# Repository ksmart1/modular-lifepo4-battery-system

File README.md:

# modular-lifepo4-battery-system
A modular LiFePO₄ battery platform with integrated monitoring, protection, and expansion.
 
# Overview

This repository documents the design and implementation of a modular LiFePO₄ battery system intended for portable power, backup energy storage, and future expansion.

The project spans power electronics, PCB design, battery management, manufacturing constraints, and mechanical considerations, and was developed iteratively with a strong emphasis on safety, serviceability, and real-world manufacturability.

## The system is composed of:

  - A battery pack PCB (2-layer and 4-layer variants)

  - A “Brain Board” responsible for regulation, monitoring, and control

  - Optional expansion / I/O boards to support charging and load sharing

  - Future 3D-printed mechanical enclosures

### Key Features

  - LiFePO₄ chemistry for improved safety and cycle life

  - Modular architecture (scalable from 4S to 8S and beyond)

  - Common-port BMS compatibility

  - High-current copper pours and busbar-style routing

  - Sense resistor–based current measurement

  - TVS, fusing, and transient protection

  - Designed for both hand assembly and low-volume fabrication

### System Architecture
  - Battery Pack PCB

  - Supports prismatic LiFePO₄ cells

  - Series connections implemented using large copper pours

  - Balance taps routed cleanly using net ties to avoid schematic ambiguity

  - Sense resistor footprint sized for tens of amps

  - Test points included for validation and debugging

### Designed in both:

  - 2-layer (cost-optimized)

  - 4-layer (improved current return and EMI behavior)

### Protection & Power Path

  - Polyfuse (40A) for fault protection

  - TVS diodes (58V) placed at charge and input connectors

  - Local ceramic decoupling at every high-current connector

### Clear separation between:

  - Battery input

  - Charger input

  - Load output

  - Brain Board

  - Buck regulation for system rails

  - MCU-based control and monitoring

  - Fuel gauge integration (BQ34Z100 family)

  - LED state-of-charge indicators

  - Designed to mate cleanly with multiple battery variants

## Design Considerations

### Manufacturing constraints were a first-class concern:

  - OSH Park vs JLCPCB tradeoffs

  - ENIG vs HASL finish

  - Stencil ordering and hand-assembly feasibility

### Hand soldering viability:

  - Component choices intentionally avoided unnecessary fine-pitch parts

  - Sense resistor installation planned explicitly for hand soldering

### Safety over aesthetics:

  - Wide copper, conservative spacing, robust grounding

### Debuggability:

  - Generous test points

  - Logical net naming

  - Clear silkscreen labeling

  - Mechanical Integration

  - PCB dimensions intentionally oversized relative to cell geometry

  - Designed to bolt into a 3D-printed, topless battery casement

### Enclosure design considers:

  - Foam isolation between cells

  - Modular splitting for printer size limitations

  - Future dovetail or fastener-based joining

### Tools & Technologies

  - KiCad (schematic + PCB layout)

  - OSH Park / JLCPCB (fabrication)

  - Inkscape (labeling / graphics)

  - 3D printing (mechanical planning)

  - Hand SMT soldering (assembly)

## Why This Project Matters

### This project demonstrates:

  - Practical power electronics design

  - Battery system safety awareness

  - PCB layout for high-current applications

  - Iterative engineering problem-solving

  - Comfort across hardware, software-adjacent design, and manufacturing

  - It reflects the type of work required in embedded systems, hardware engineering, robotics, energy systems, and applied cybersecurity/assurance roles where understanding      the entire system matters.

### Status

  - Battery PCB (4S and 8S variants): Complete

  - Expansion / I/O board: Complete

  - Assembly and validation: In progress

  - Enclosure design: Complete

  - Future revisions: Expected

Disclaimer

This project is for educational and experimental purposes.
Working with high-current lithium batteries carries inherent risk.
Use appropriate safety precautions and do not deploy designs without proper validation.

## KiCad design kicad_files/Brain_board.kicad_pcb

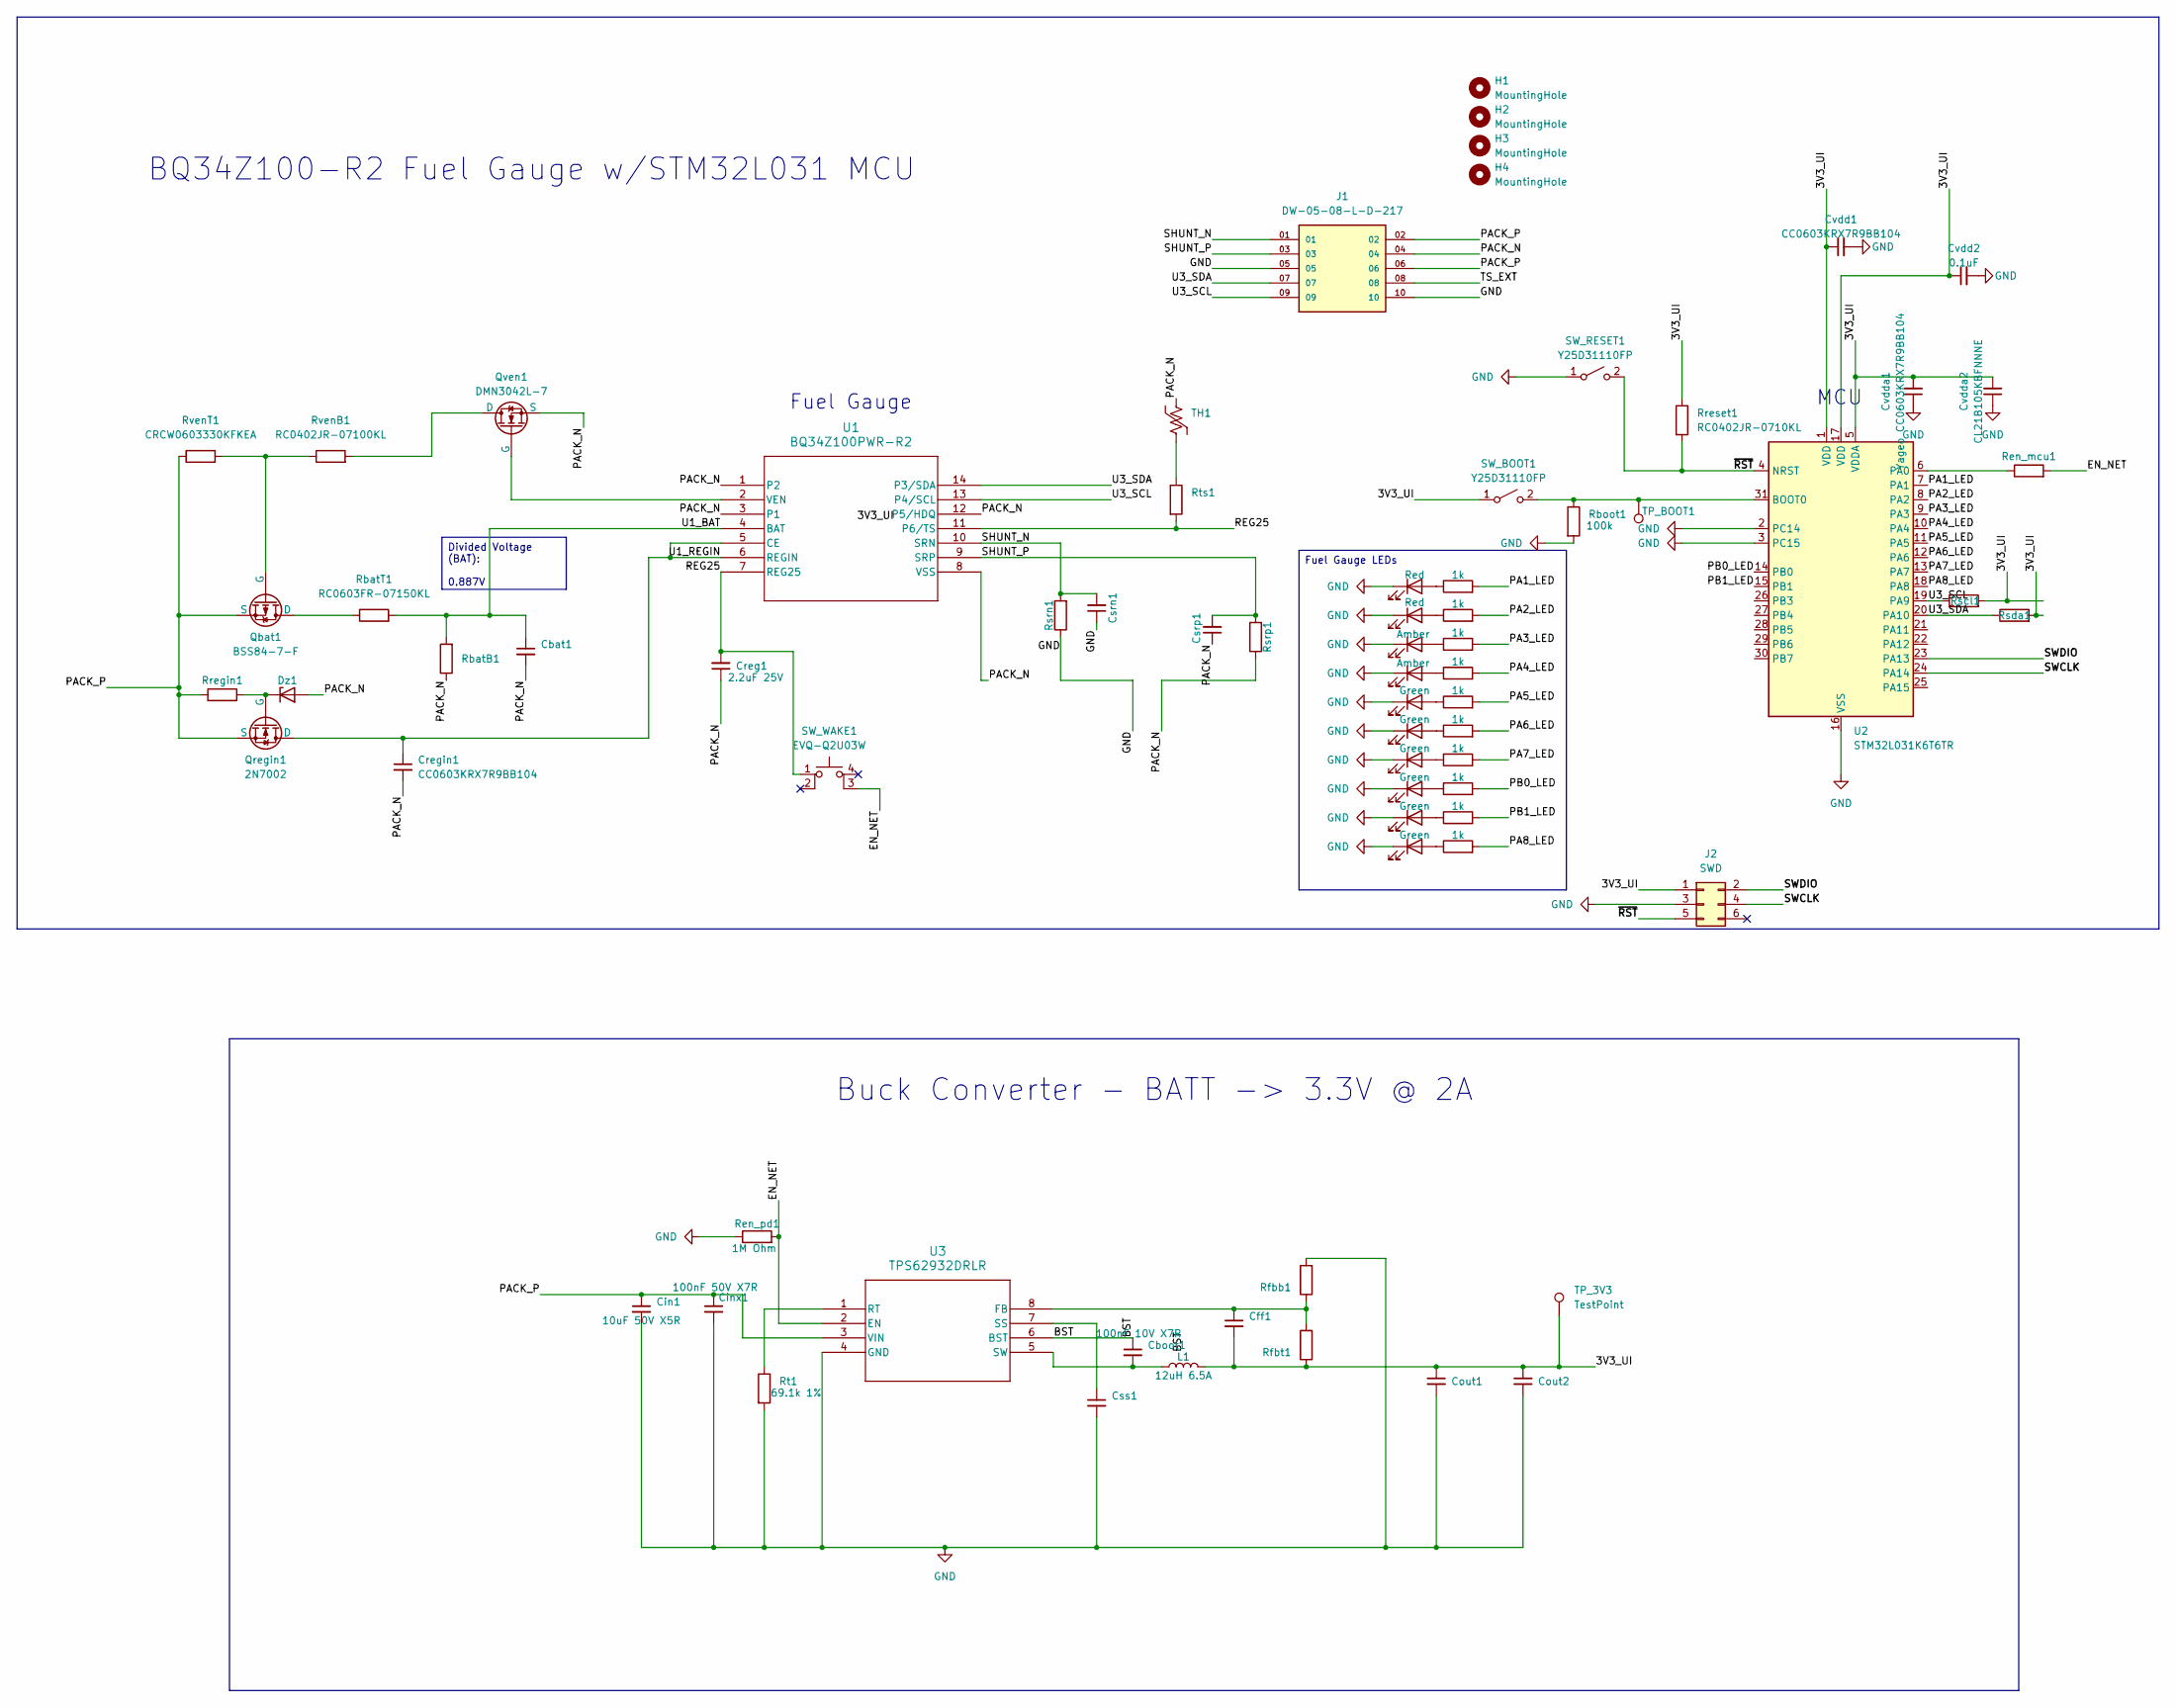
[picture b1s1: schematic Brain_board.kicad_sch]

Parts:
Cbat1: GRM1885C1H332JA01D; C_0603_1608Metric
Cboot1: CC0603KRX7R9BB104; C_0603_1608Metric
Cff1: C0603C560J5GACTU; C_0603_1608Metric
Cin1: CL31A106KBHNNNE; C_1206_3216Metric
Cinx1: CC0603KRX7R9BB104; C_0603_1608Metric
Cout1: GRM31CR61A476ME15L; C_1210_3225Metric
Cout2: GRM32ER61C476KE15L; C_1210_3225Metric
Creg1: GMC10X7R225K25NT; C_0603_1608Metric
Cregin1: CC0603KRX7R9BB104; C_0603_1608Metric
Csrn1: CC0603KRX7R9BB104; C_0603_1608Metric
Csrp1: CC0603KRX7R9BB104; C_0603_1608Metric
Css1: GRM155R71A333KA01D; C_0402_1005Metric
Cvdd1: CC0603KRX7R9BB104; C_0603_1608Metric
Cvdd2: 0.1uF; C_0603_1608Metric
Cvdda1: Yageo CC0603KRX7R9BB104; C_0603_1608Metric
Cvdda2: CL21B105KBFNNNE; C_0805_2012Metric
D1, D2, D3, D4, D5, D6: 5988170107F; LED_0805_2012Metric_Pad1.15x1.40mm_HandSolder
D7, D8: B1701UY--20D000214U1930; LED_0805_2012Metric_Pad1.15x1.40mm_HandSolder
D9, D10: B1701URO-20D000114U1930; LED_0805_2012Metric_Pad1.15x1.40mm_HandSolder
Dz1: BZT52C5V6T-7; D_SOD-523
H1, H2, H3, H4: MountingHole; MountingHole_3.2mm_M3
J1: DW-05-08-L-D-217; SAMTEC_DW-05-X-X-D-X; PARTREV 01-06-94
J2: SWD; CON6_2X3_DU_FTSH_SAI
L1: SRR1208-120ML; L_Bourns_SRR1208_12.7x12.7mm
Qbat1: BSS84-7-F; SOT-23-3
Qregin1: 2N7002; SOT-23-3
Qven1: DMN3042L-7; SOT-23-3
RbatB1: RC0603FR-074K7L; R_0603_1608Metric
RbatT1: RC0603FR-07150KL; R_0603_1608Metric
Rboot1: RC0402JR-07100KL; R_0402_1005Metric
Ren_mcu1: RC0402JR-0710KL; R_0402_1005Metric
Ren_pd1: CRCW06031M00FKEA; R_0603_1608Metric
Rfbb1: RC0402JR-0710KL; R_0402_1005Metric
Rfbt1: CRCW040230K9FKED; R_0402_1005Metric
Rled1, Rled2, Rled3, Rled4, Rled5, Rled6, Rled7, Rled8, Rled9, Rled10: RMCF0603FT1K00; R_0603_1608Metric_Pad0.98x0.95mm_HandSolder
Rregin1: RC0402JR-0710KL; R_0402_1005Metric
Rreset1: RC0402JR-0710KL; R_0402_1005Metric
Rscl1: RC0603FR-074K7L; R_0402_1005Metric
Rsda1: RC0603FR-074K7L; R_0402_1005Metric
Rsrn1: CRCW0603100RFKEA; R_0603_1608Metric
Rsrp1: CRCW0603100RFKEA; R_0603_1608Metric
Rt1: CRCW060361K9FKEA; R_0603_1608Metric
Rts1: RC0402JR-0710KL; R_0402_1005Metric
RvenB1: RC0402JR-07100KL; R_0402_1005Metric
RvenT1: CRCW0603330KFKEA; R_0603_1608Metric
SW_BOOT1: Y25D31110FP; KXT 311 LHS_CNK
SW_RESET1: Y25D31110FP; KXT 311 LHS_CNK
SW_WAKE1: EVQ-Q2U03W; EVQQ2_3_PAN
TH1: 103KT1608T-1P; R_0603_1608Metric
TP_3V3: TestPoint; TestPoint_Pad_D1.5mm
TP_BOOT1: TestPoint; TestPoint_Pad_D1.5mm
U1: BQ34Z100PWR-R2; PW14_TEX
U2: STM32L031K6T6TR; LQFP-32_7x7mm_P0.8mm
U3: TPS62932DRLR; SOT8_DRL_TEX

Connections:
/3V3_UI: Cff1.2, Cout1.1, Cout2.1, Cvdd1.1, Cvdd2.1, Cvdda1.2, Cvdda2.2, J2.1, L1.2, Rfbt1.1, Rreset1.1, Rscl1.2, Rsda1.2, SW_BOOT1.1 (A), TP_3V3.1, U2.1 (VDD), U2.5 (VDDA), U2.17 (VDD)
/BST: Cboot1.1, U3.6 (BST)
/EN_NET: Ren_mcu1.2, Ren_pd1.2, SW_WAKE1.3 (K), U3.2 (EN)
/PA1_LED: Rled10.2, U2.7 (PA1)
/PA2_LED: Rled9.2, U2.8 (PA2)
/PA3_LED: Rled8.2, U2.9 (PA3)
/PA4_LED: Rled7.2, U2.10 (PA4)
/PA5_LED: Rled6.2, U2.11 (PA5)
/PA6_LED: Rled5.2, U2.12 (PA6)
/PA7_LED: Rled4.2, U2.13 (PA7)
/PA8_LED: Rled1.2, U2.18 (PA8)
/PACK_N: Cbat1.2, Creg1.1, Cregin1.2, Csrp1.1, Dz1.2 (A), J1.04, Qven1.3 (S), RbatB1.1, Rsrp1.1, TH1.1, U1.1 (P2), U1.3 (P1), U1.8 (VSS), U1.12 (P5/HDQ)
/PACK_P: Cin1.1, Cinx1.1, J1.02, J1.06, Qbat1.3 (S), Qregin1.3 (S), Rregin1.1, RvenT1.1, U3.3 (VIN)
/PB0_LED: Rled3.2, U2.14 (PB0)
/PB1_LED: Rled2.2, U2.15 (PB1)
/REG25: Creg1.2, Rts1.2, SW_WAKE1.1, U1.7 (REG25), U1.11 (P6/TS)
/SHUNT_N: Csrn1.2, J1.01, Rsrn1.2, U1.10 (SRN)
/SHUNT_P: Csrp1.2, J1.03, Rsrp1.2, U1.9 (SRP)
/SWCLK: J2.4, U2.24 (PA14)
/SWDIO: J2.2, U2.23 (PA13)
/TS_EXT: J1.08
/U1_BAT: Cbat1.1, RbatB1.2, RbatT1.2, U1.4 (BAT)
/U1_REGIN: Cregin1.1, Qregin1.1 (D), U1.5 (CE), U1.6 (REGIN)
/U3_SCL: J1.09, Rscl1.1, U1.13 (P4/SCL), U2.19 (PA9)
/U3_SDA: J1.07, Rsda1.1, U1.14 (P3/SDA), U2.20 (PA10)
/~RST: J2.5, Rreset1.2, SW_RESET1.2 (B), U2.4 (NRST)
GND: Cin1.2, Cinx1.2, Cout1.2, Cout2.2, Csrn1.1, Css1.2, Cvdd1.2, Cvdd2.2, Cvdda1.1, Cvdda2.1, D1.1 (K), D2.1 (K), D3.1 (K), D4.1 (K), D5.1 (K), D6.1 (K), D7.1 (K), D8.1 (K), D9.1 (K), D10.1 (K), J1.05, J1.10, J2.3, Rboot1.2, Ren_pd1.1, Rfbb1.2, Rsrn1.1, Rt1.2, SW_RESET1.1 (A), U2.2 (PC14), U2.3 (PC15), U2.16 (VSS), U2.32 (VSS), U3.4 (GND)
unnamed: D1.2 (A), Rled1.1
unnamed: D2.2 (A), Rled2.1
unnamed: D3.2 (A), Rled3.1
unnamed: D4.2 (A), Rled4.1
unnamed: D5.2 (A), Rled5.1
unnamed: D6.2 (A), Rled6.1
unnamed: D7.2 (A), Rled7.1
unnamed: D8.2 (A), Rled8.1
unnamed: D9.2 (A), Rled9.1
unnamed: D10.2 (A), Rled10.1
unnamed: Dz1.1 (K), Qregin1.2 (G), Rregin1.2
unnamed: Qbat1.1 (D), RbatT1.1
unnamed: Qbat1.2 (G), RvenB1.1, RvenT1.2
unnamed: Qven1.1 (D), RvenB1.2
unnamed: Qven1.2 (G), U1.2 (VEN)
unnamed: Rts1.1, TH1.2
unnamed: Rboot1.1, SW_BOOT1.2 (B), TP_BOOT1.1, U2.31 (BOOT0)
unnamed: Ren_mcu1.1, U2.6 (PA0)
unnamed: Cff1.1, Rfbb1.1, Rfbt1.2, U3.8 (FB)
unnamed: Rt1.1, U3.1 (RT)
unnamed: Css1.1, U3.7 (SS)
unnamed: Cboot1.2, L1.1, U3.5 (SW)

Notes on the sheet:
Fuel Gauge
BQ34Z100-R2 Fuel Gauge w/STM32L031 MCU
MCU
Buck Converter - BATT -> 3.3V @ 2A
Divided Voltage (BAT): 0.887V
Fuel Gauge LEDs

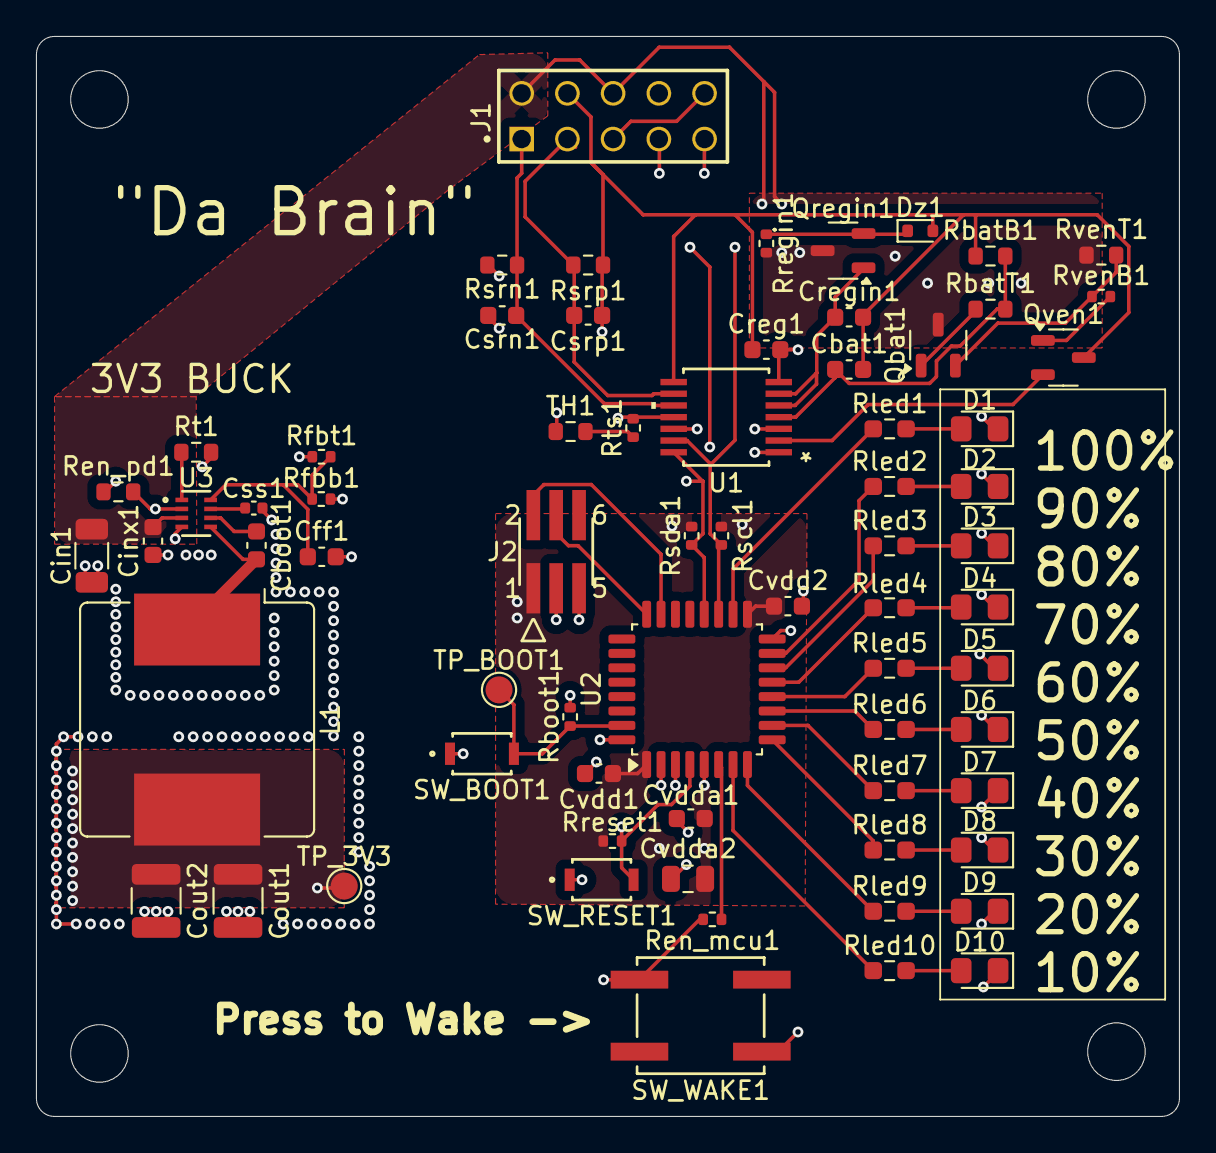
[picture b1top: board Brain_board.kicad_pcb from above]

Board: 4 copper layers, 63.5 x 60.0 mm, 73 parts (0 on the bottom side), 48 nets.

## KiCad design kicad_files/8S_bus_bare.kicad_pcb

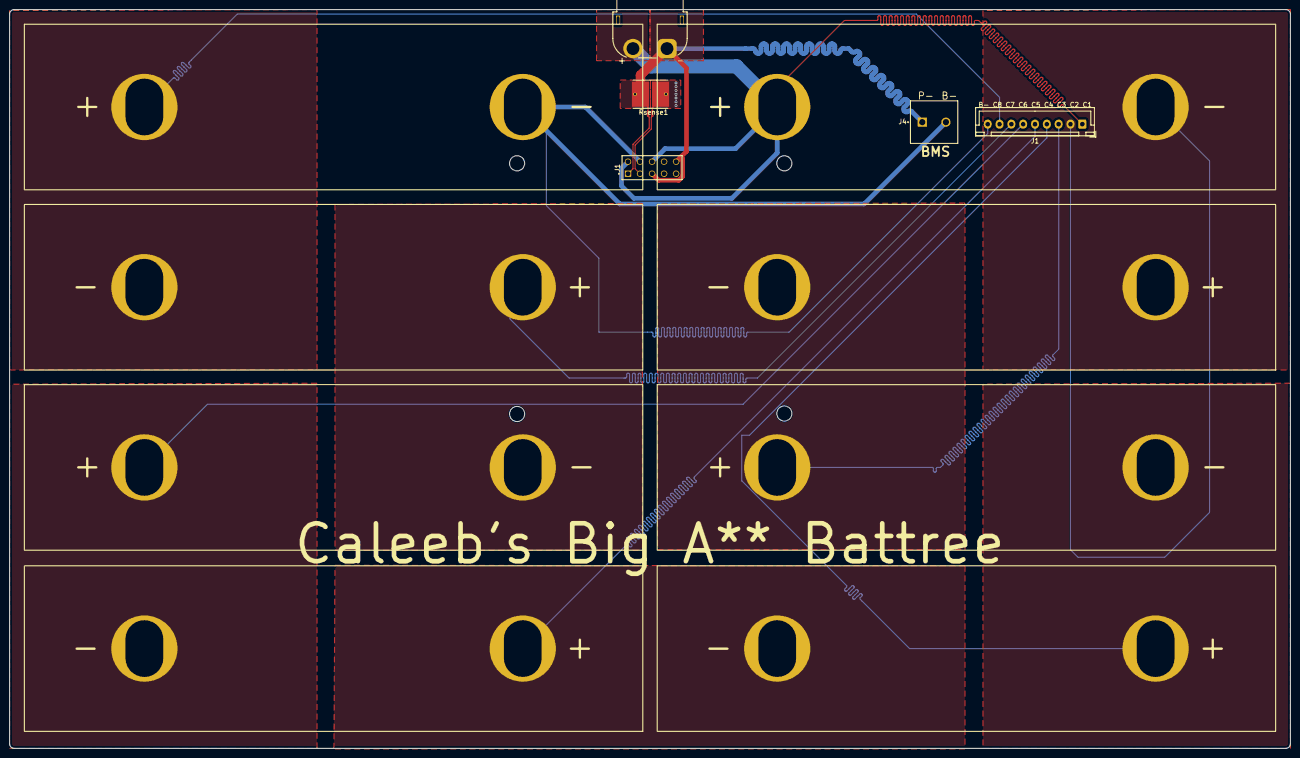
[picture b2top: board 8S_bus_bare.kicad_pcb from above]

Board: 2 copper layers, 270.8 x 156.2 mm, 17 parts (0 on the bottom side), 10 nets.

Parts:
BT1, BT2, BT3, BT4, BT5, BT6, BT7, BT8: Battery_Cell; Battery_Narada_50Ah_LiFePO4
H1, H2, H3, H4: MountingHole; MountingHole_3.2mm_M3
J1: HW-05-08-F-D-250-SM; SAMTEC_DW-05-X-X-D-X
J1#2: Balance Conn; JST_XH_B9B-XH-A_1x09_P2.50mm_Vertical
J3: XT60; AMASS_XT60PW-F_1x02_P7.20mm_Horizontal
J4: BMS; PHOENIX_1935776
Rsense1: 1m 1W 1%; RESC_WSHM2818R0150FEA

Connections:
/BT1+: BT1.1 (+), BT2.2 (-), J1#2.8
/BT2+: BT2.1 (+), BT3.2 (-), J1#2.7
/BT3+: BT3.1 (+), BT4.2 (-), J1#2.6
/BT4+: BT4.1 (+), BT5.2 (-), J1#2.5
/BT5+: BT5.1 (+), BT6.2 (-), J1#2.4
/BT6+: BT6.1 (+), BT7.2 (-), J1#2.3
/BT7+: BT7.1 (+), BT8.2 (-), J1#2.2
/PACK_N: BT1.2 (-), J1.04, J1#2.9, J4.2, Rsense1.1, Rsense1.2
/PACK_P: BT8.1 (+), J1.02, J1.06, J1#2.1, J3.2
GND: J1.05, J1.10, J3.1, J4.1, Rsense1.3, Rsense1.4

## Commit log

2025-12-20 Enhance README with comprehensive project details
    Expanded README with detailed project overview, features, architecture, design considerations, tools, and project status.
2025-12-20 Update README.md
    Added formatting
2025-12-20 Revise README with project name and overview
    Updated project name and added overview section.
2025-12-20 Update README with improved structure and headings
2025-12-24 Rename 8S_bus_bare.kicad_pcb to kicad_files/8S_bus_bare.kicad_pcb
2025-12-24 Rename 8S_bus_bare.kicad_sch to kicad_files/8S_bus_bare.kicad_sch
2025-12-24 Rename 8S_bus_bare.zip to kicad_files/8S_bus_bare.zip
2025-12-24 Rename designators.csv to busbar_designators.csv
2025-12-24 Rename netlist.ipc to busbar_netlist.ipc
2025-12-24 Add busbar_positions.csv file
2025-12-24 Rename designators.csv to BrainBoard_designators.csv
2025-12-24 Rename netlist.ipc to BrainBoard_netlist.ipc
